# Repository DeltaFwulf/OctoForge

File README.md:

# OctoForge: 
A work in progress electric furnace capable of reaching chamber temperatures of 1200 C.

This project is simply a display of technical knowledge and something through which we have learned further technologies. The hope is that any projects tackled in the future will be easier due to the experience and skills learned here.

There are three main areas of which the furnace is comprised:
- Mechanical - Frame design complete and in production, insulation under final design iteration, heating element under final design iteration.
- Power electronics - Still iterating over design and testing.
- Control electronics - Yet to be started.

Progress is being tracked [here](https://github.com/users/DeltaFwulf/projects/2).

## How to use this project?
The following software is required to view the various CAD files:
- FreeCAD-1.0.2
- KiCAD-9.0

## How to reproduce OctoForge?
- Sheet metal components were ordered from [Fractory](https://fractory.com/) with the following parameters:
  - Thicknesses:
    - Plates: 3mm
    - Lower panels: 2mm
    - Upper panels: 1.5mm
    - Lid: 2mm
  - High temperature components will be black oxide treated, and exterior components will be painted with high temperature paint and clear coat.
- The other mechanical components were machined from stock using the drawings provided within the CAD directory.
- Fittings were ordered using the provided [BOM](Documentation/Mechanical/BOM.ods) from [Accu](https://www.accu.co.uk/) and [Vital Parts](https://www.vital-parts.co.uk/).
- Feet and handles are standard components, but were sourced from WDS components as listed in the BOM.
- PCBs were ordered from [JLCPCB](jlcpcb.com) with the following parameters:
  - 2 layers
  - PCB thickness - 1.6mm
  - Material type - TG135
  - Outer copper weight - 1oz

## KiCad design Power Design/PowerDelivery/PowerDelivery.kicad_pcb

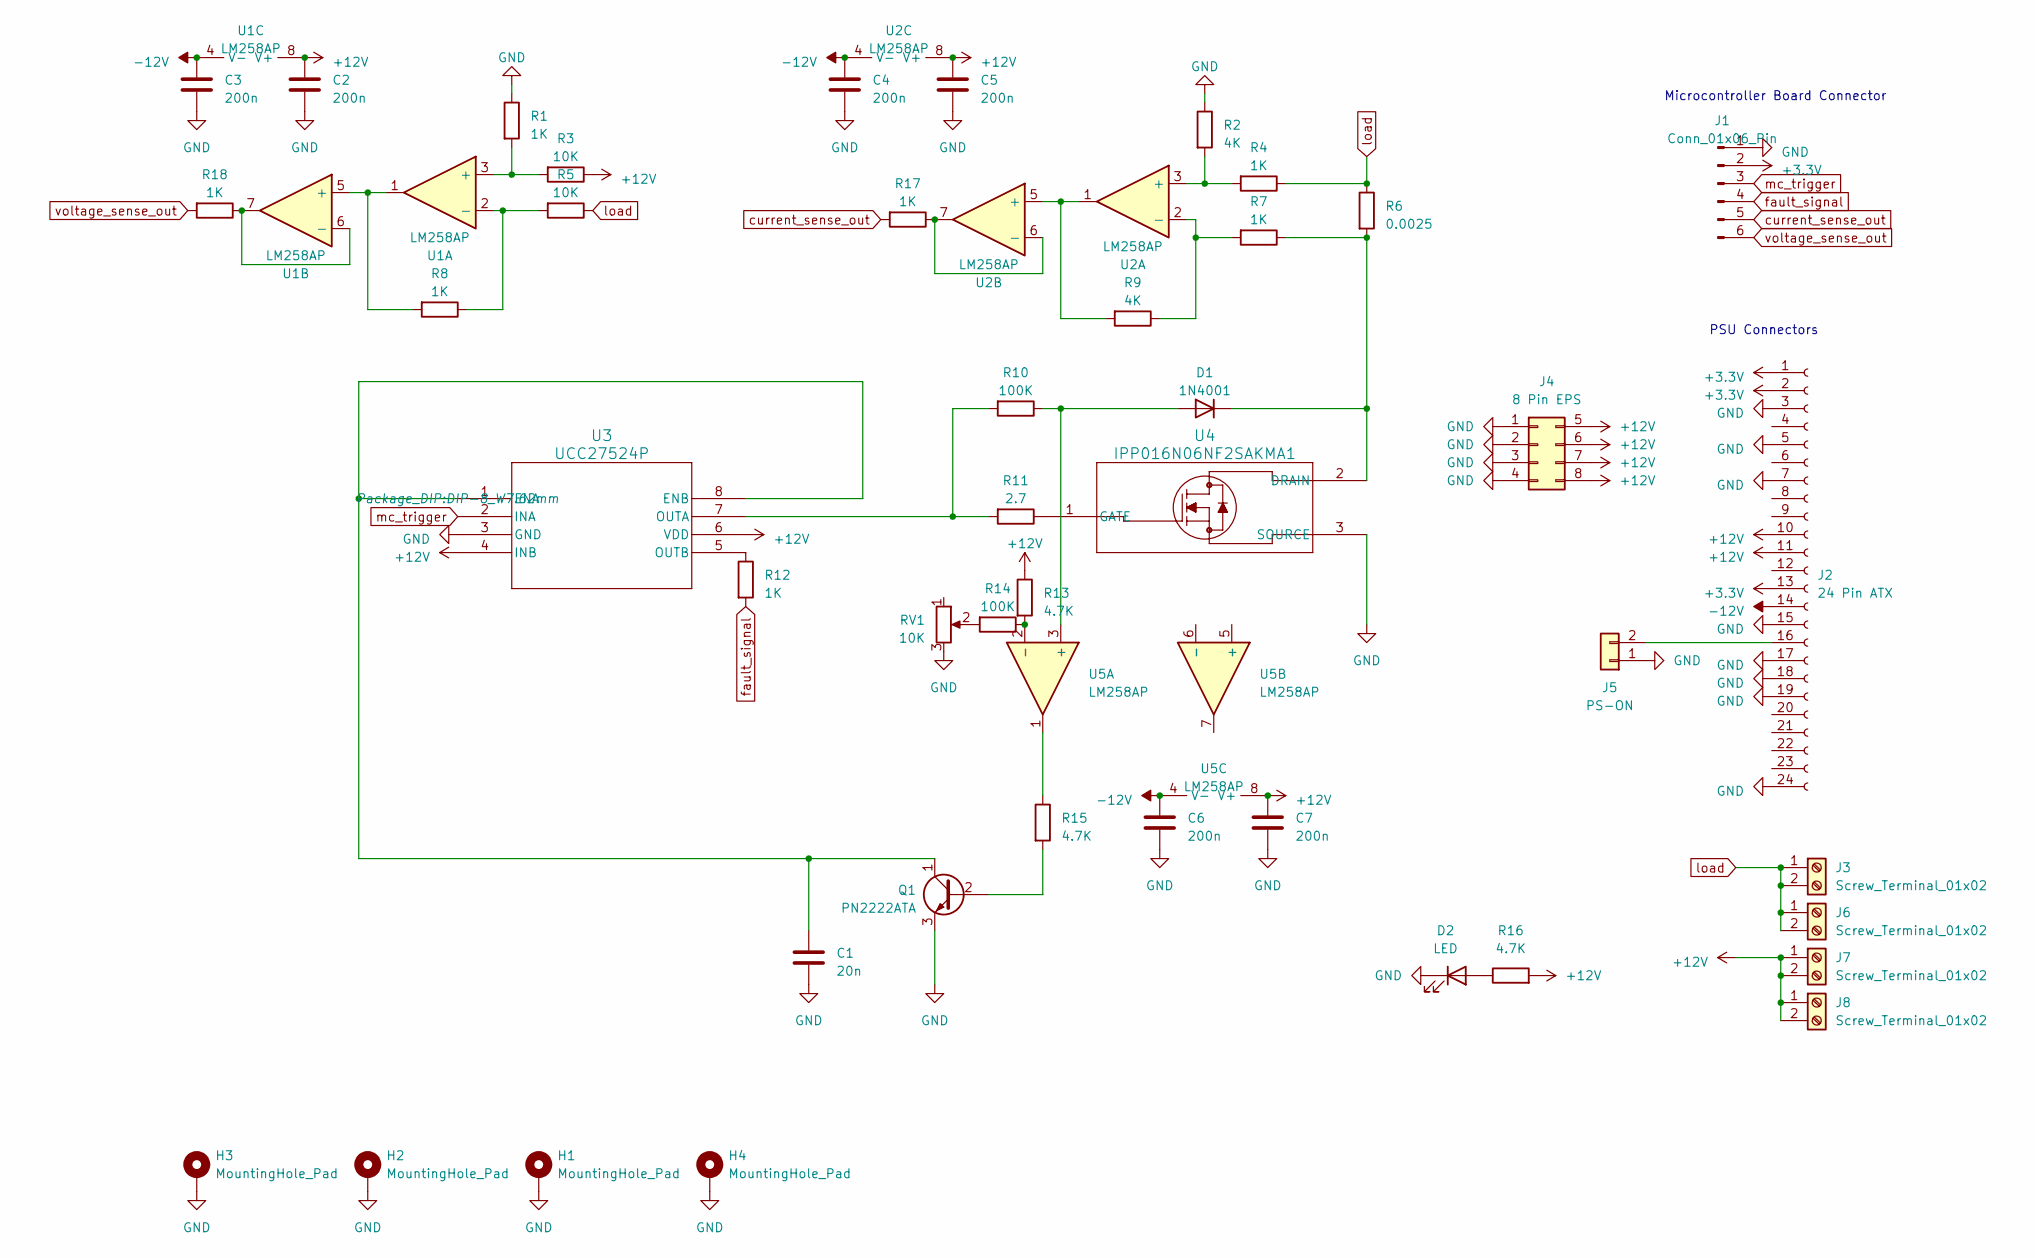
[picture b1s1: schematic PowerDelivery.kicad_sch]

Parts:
C1: 20n; C_Disc_D3.8mm_W2.6mm_P2.50mm
C2, C3, C4, C5, C6, C7: 200n; C_Disc_D3.8mm_W2.6mm_P2.50mm
D1: 1N4001; D_DO-41_SOD81_P7.62mm_Horizontal
D2: LED; LED_D5.0mm
H1, H2, H3, H4: MountingHole_Pad; MountingHole_3.2mm_M3_ISO7380_Pad
J1: Conn_01x06_Pin; PinHeader_1x06_P2.54mm_Vertical
J2: 24 Pin ATX; Molex_Mini-Fit_Jr_5566-24A_2x12_P4.20mm_Vertical
J3, J6, J7, J8: Screw_Terminal_01x02; TerminalBlock_bornier-2_P5.08mm
J4: 8 Pin EPS; Molex_Mini-Fit_Jr_5566-08A_2x04_P4.20mm_Vertical
J5: PS-ON; PinHeader_1x02_P2.54mm_Vertical
Q1: PN2222ATA; TO-92_Wide
R1, R4, R7, R8, R12, R17, R18: 1K; R_Axial_DIN0207_L6.3mm_D2.5mm_P7.62mm_Horizontal
R2, R9: 4K; R_Axial_DIN0207_L6.3mm_D2.5mm_P7.62mm_Horizontal
R3, R5: 10K; R_Axial_DIN0207_L6.3mm_D2.5mm_P7.62mm_Horizontal
R6: 0.0025; R_Axial_DIN0617_L17.0mm_D6.0mm_P20.32mm_Horizontal
R10, R14: 100K; R_Axial_DIN0207_L6.3mm_D2.5mm_P7.62mm_Horizontal
R11: 2.7; R_Axial_DIN0207_L6.3mm_D2.5mm_P7.62mm_Horizontal
R13, R15, R16: 4.7K; R_Axial_DIN0207_L6.3mm_D2.5mm_P7.62mm_Horizontal
RV1: 10K; Potentiometer_Bourns_3296W_Vertical
U1, U2, U5: LM258AP; DIP-8_W7.62mm
U3: UCC27524P; DIP-8_W7.62mm
U4: IPP016N06NF2SAKMA1; TO-220-3_Horizontal_TabDown

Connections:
+3.3V: J1.2, J2.1, J2.2, J2.13
+12V: C2.1, C5.1, C7.1, J2.10, J2.11, J4.5, J4.6, J4.7, J4.8, J7.1, J7.2, J8.1, J8.2, R3.1, R13.1, R16.2, U1.8 (V+), U2.8 (V+), U3.4 (INB), U3.6 (VDD), U5.8 (V+)
-12V: C3.1, C4.1, C6.1, J2.14, U1.4 (V-), U2.4 (V-), U5.4 (V-)
GND: C1.2, C2.2, C3.2, C4.2, C5.2, C6.2, C7.2, D2.1 (K), H1.1, H2.1, H3.1, H4.1, J1.1, J2.3, J2.5, J2.7, J2.15, J2.17, J2.18, J2.19, J2.24, J4.1, J4.2, J4.3, J4.4, J5.1, Q1.3 (E), R1.1, R2.1, RV1.3, U3.3 (GND), U4.3 (SOURCE)
unnamed: D1.2 (A), R10.1, U5.3 (+)
unnamed: D1.1 (K), R6.2, R7.1, U4.2 (DRAIN)
unnamed: D2.2 (A), R16.1
unnamed: J2.16, J5.2
unnamed: Q1.2 (B), R15.2
unnamed: C1.1, Q1.1 (C), U3.1 (ENA), U3.8 (ENB)
unnamed: R14.2, RV1.2
unnamed: R15.1, U5.1
unnamed: R1.2, R3.2, U1.3 (+)
unnamed: R5.2, R8.1, U1.2 (-)
unnamed: R8.2, U1.1, U1.5 (+)
unnamed: R18.1, U1.6 (-), U1.7
unnamed: R2.2, R4.2, U2.3 (+)
unnamed: R7.2, R9.1, U2.2 (-)
unnamed: R9.2, U2.1, U2.5 (+)
unnamed: R17.1, U2.6 (-), U2.7
unnamed: R10.2, R11.2, U3.7 (OUTA)
unnamed: R12.1, U3.5 (OUTB)
unnamed: R11.1, U4.1 (GATE)
unnamed: R13.2, R14.1, U5.2 (-)
current_sense_out: J1.5, R17.2
fault_signal: J1.4, R12.2
load: J3.1, J3.2, J6.1, J6.2, R4.1, R5.1, R6.1
mc_trigger: J1.3, U3.2 (INA)
voltage_sense_out: J1.6, R18.2

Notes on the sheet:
PSU Connectors
Microcontroller Board Connector

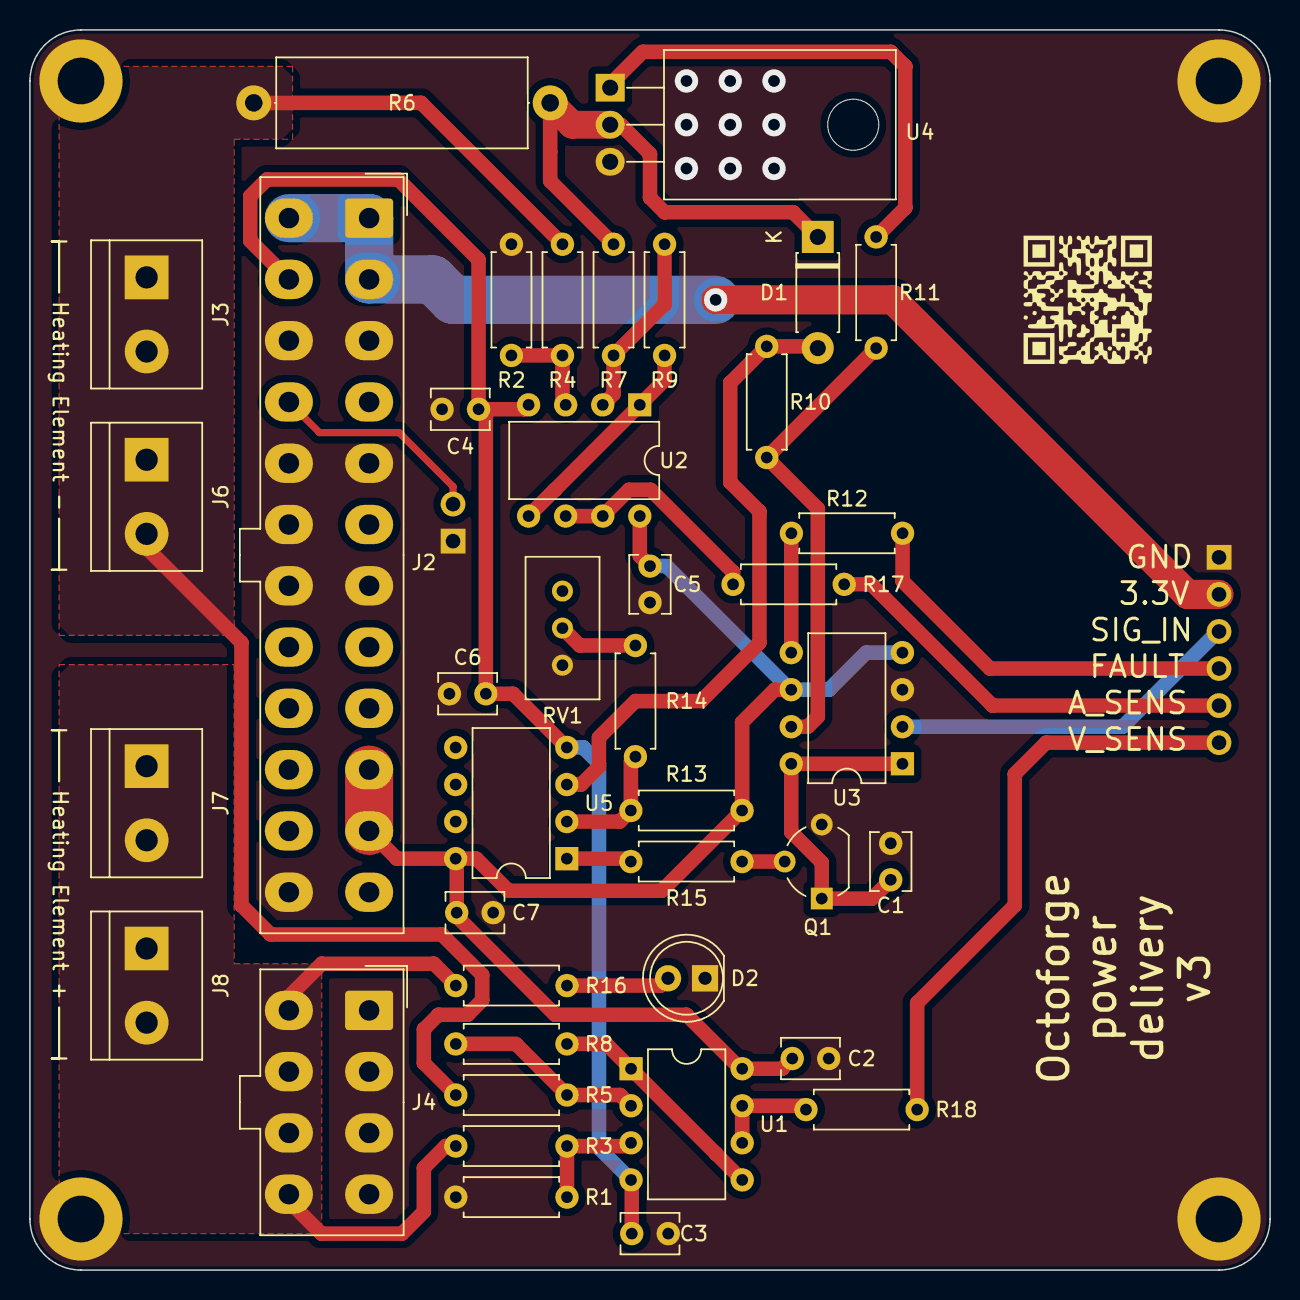
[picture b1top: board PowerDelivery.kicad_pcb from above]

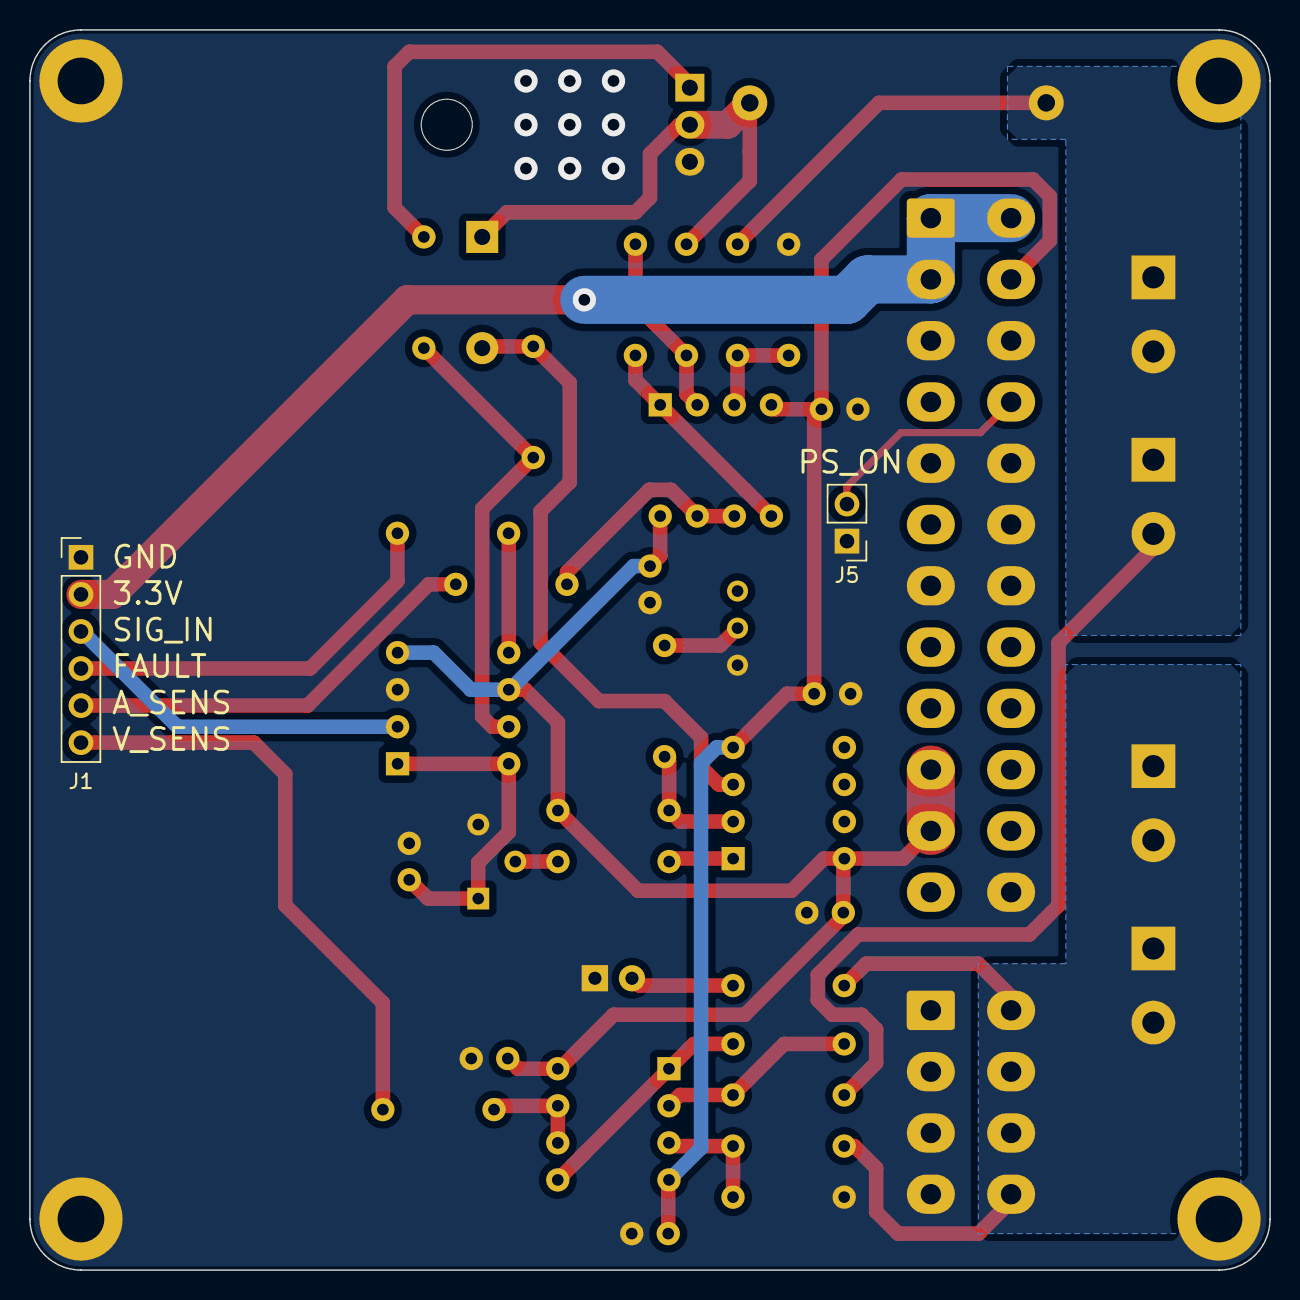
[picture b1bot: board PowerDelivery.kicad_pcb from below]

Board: 2 copper layers, 85.0 x 85.0 mm, 46 parts (2 on the bottom side), 29 nets.

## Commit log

2023-08-18 added obsidian files
    moved files into correct directory
2023-08-18 Create README.md
    Another one
2023-08-18 example file structure
2023-08-18 started chamber loss model
    started to model heat loss resistance network for chamber walls
2023-08-19 updated devLog
    description of analysis methods and chamber model code started
2023-08-20 implemented design point solver
    I have implemented a convoluted solver to get key furnace performance data at a single chamber temperature and power. It's currently having weird complex number issues but this will hopefully not be 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
2023-08-28 fixed shooting method solvers
    There were incorrect references to g1 in both e1 and e2 calculations. Also, created simple plotting tools to see how variables correlate.
2023-09-03 inner wall fixed as chamber temperature
    Modelled the furnace as having its inner wall surface temperature equal to the chamber temperature in an attempt to fix suspected underprediction of heat loss
2023-09-04 begun DevLog
2023-09-04 finished evaluation of first MOSFET
2023-09-04 edited the frequency bit
2023-09-06 06/09/23 DevLog updates
2023-09-09 09/09/23 DevLog updates
2023-09-09 added lid/base losses, multilayer walls
    I have included capability to model n-layer walls, as well as including conservative estimates for lid and base heat losses.
2023-09-09 added plots
    tidied up the devlog slightly and added a few plots to the 'plots' folder in thermal analysis
2023-10-06 added heating elements
    working out how to create larger assemblies in FreeCAD
2023-10-06 added another simulation
2023-10-06 kicad project
2023-10-08 Update README.md
    added a basic description of the furnace
2023-10-09 exoskeleton begins
    modelled casing base and side panels
2023-11-11 further pcb work
2024-01-01 moved connectors and added mounting holes
2024-01-02 designed furnace frame
    An initial furnace frame has been designed and modelled in freeCAD. Insulation has been partially modelled.
2024-01-21 thickened traces
2024-01-21 removed uneccessary trace
2024-01-21 lid tweaks
    lid made more cheaperer
2024-01-22 initial commit on controller pcb
2024-01-22 small changes
2024-01-24 updated dev log
2024-01-25 devlog: concerns with power
2024-01-25 cleaned up schematic
2024-02-02 replaced hinge
    updated hinge to match final component
2024-02-07 updated front panel
    changed front panel cut-out to individual components, modelled PCB cooling duct, added BOM to mechanical design.
2024-02-15 updated chamber bricks
    - element holes split over two bricks
    - thermocouple hole included
2024-04-14 refactored thermal model
    added temperature distribution plotter and renamed symbols for easier reading.
2024-10-12 update to Kicad 8
2024-10-12 Create power delivery V2
2024-10-18 Change implemented
2024-10-19 began revision 2 assembly
    began drawing a native assembly based version of Octoforge in FreeCAD
2024-10-19 continued frame design
    most of the frame has been remodelled.
2024-10-23 Remaining files to be commited
2024-10-24 lower frame redrawn
    the lower frame and panels have been included in the rev2 assembly. BOM updated
2024-11-23 update branch 16
2024-12-03 reworked assembly up to lid section
    native assembly has been remade with fixed constrains up to the chamber bricks and frame main body.
2024-12-14 began lid model
    the lid has been redesigned for better thermal performance. Modelling has begun with the brick and frame profile modelled so far.
2024-12-20 frame redesign completed
    The majority of the redesign has been completed, the only major details remaining are the electrical components and handles.
2024-12-29 power terminals
    The power terminals have been included in the assembly, as well as handle holes for carry handles.
2025-04-20 furnace assembly B
    Due to cost constraints, the furnace was revisioned to B, with a redesigned lower section for lower cost, compactness, and ease of assembly.
2025-10-18 Made changes from v3
2025-10-18 created Gerber.zip
2026-02-06 updated brackets
    Changed cut to 45 degree on brackets for ease of manufacture.
2026-02-07 updated frame bracket design
    Changed holes to 4.2 mm, added part drawings.
2026-02-07 Tidy up file structure
2026-02-09 reworked lower blocks, upper panels
    Added block brackets for lower panels, upper panels, and upper panel brackets.
2026-02-14 updated frame components
    remodelled panel blocks, upper panels, upper panel brackets.
2026-02-15 added frame fasteners
    Included fasteners holding frame together and lifting handle fasteners.
2026-02-16 added final fasteners to the frame
    Fasteners have been added to the lid hinge.
2026-02-16 added lid handle
    Sourced a lid handle, included in GA and added associated fasteners.
2026-02-20 began work on BOM
    Renamed assembly components and reworked lid hinge fasteners for better visibility in BOM
2026-02-22 rebuilt fastener parts to appear on fastener BOM
    The BOM tools provided by FreeCAD's Assembly and Fastener WBs will now populate with all components, with reasonable part names. Added an explanation as to how this was done in design journal.
2026-02-22 added BOM
    The BOM now contains up to date information about the frame components, as of 22/02/2026.
2026-02-22 updated OCT-LFPNL-CA design to complete
    ATX PSU panel OCT-LFPNL-CA was corrected against known good mounting pattern. BOM updated with stock / buy information.
2026-02-22 Replaced old COTS components
    Updated COTS component CAD and BOM entries where better alternatives were found. The front lower panel (OCT-LFPNL-BA) has been marked as design complete.
2026-03-03 README updated regarding mechanical stuff
2026-03-04 began heating element sizing calculations
2026-03-05 preliminary element geometry
    The heating element geometry has a preliminary solution and basic CAD model. The furnace chamber bricks have also been remodelled within a single file named OCT-CHMBR-A
2026-03-07 heating element modelled
    OCT-HWIRE-AA has been modelled using some FreeCAD dark magic.
2026-03-08 heating elements included in GA (#48)
    The GA model now has the heating elements included.
2026-03-08 updated BOM
    Corrected heating element file name to OCT-HELEM-A, updated Bill of Materials to current status.
2026-03-10 Improved heating element render performance
    The angular deflection has been relaxed from 6.4 degrees to 15 degrees, reducing rendering overhead and reducing recompute times.
2026-03-13 added insulation components
2026-04-12 updated frame assembly to FreeCAD 1.1, updated lower panel threaded brackets, top hinge bracket
2026-04-12 Re-applied frame assembly updates which applied incorrectly in previous commit.
2026-04-18 Added threaded mid brackets as OCT-UTBRK-AA
2026-04-18 Updated BOM
